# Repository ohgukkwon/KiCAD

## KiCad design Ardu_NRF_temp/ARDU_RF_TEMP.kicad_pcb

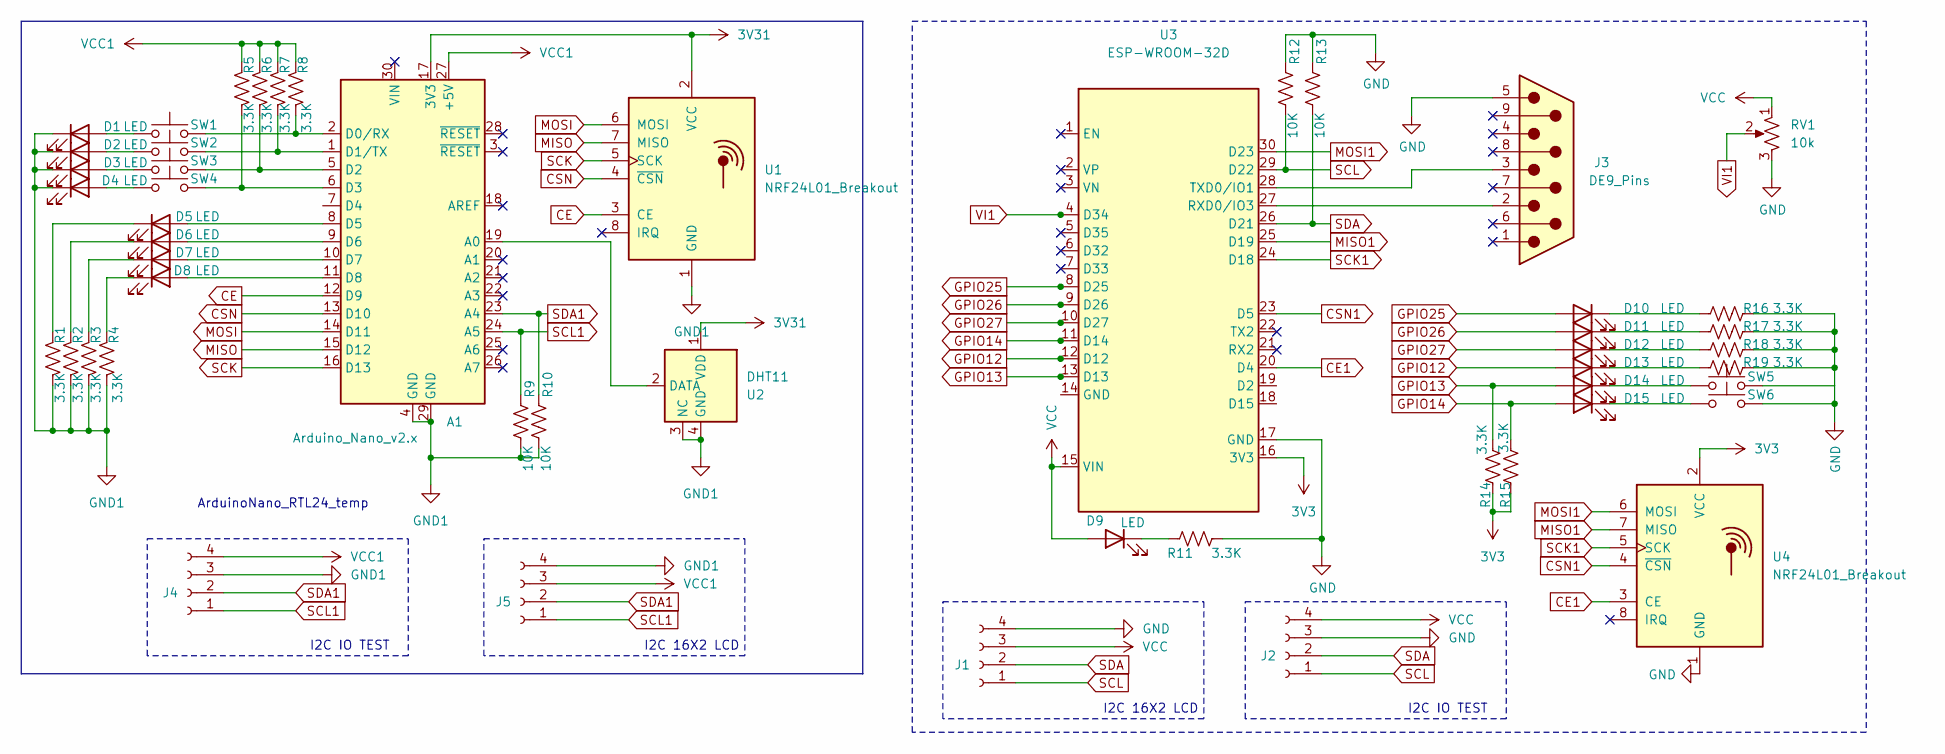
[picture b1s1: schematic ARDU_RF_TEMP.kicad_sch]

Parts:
A1: Arduino_Nano_v2.x; Arduino_Nano
D1, D2, D3, D4, D5, D6, D7, D8, D9, D10, D11, D12, D13, D14, D15: LED; LED_D3.0mm_Horizontal_O1.27mm_Z2.0mm
J1, J5: Conn_01x04_Socket; CONN_PPPC041LGBN-RC_SUL
J2, J4: Conn_01x04_Socket; CONN_PPTC041LFBN-RC_SUL
J3: DE9_Pins; DSUB-9_Pins_Vertical_P2.77x2.84mm_MountingHoles
R1, R2, R3, R4, R5, R6, R7, R8, R11, R14, R15, R16, R17, R18, R19: 3.3K; R_Axial_DIN0207_L6.3mm_D2.5mm_P10.16mm_Horizontal
R9, R10, R12, R13: 10K; R_Axial_DIN0207_L6.3mm_D2.5mm_P10.16mm_Horizontal
RV1: 10k; Potentiometer_Alps_RK163_Single_Horizontal
SW1, SW2, SW3, SW4, SW5, SW6: SW_Push; SW_Tactile_SPST_NO_Straight_CK_PTS636Sx25SMTRLFS
U1, U4: NRF24L01_Breakout; nRF24L01_Breakout
U2: DHT11; Aosong_DHT11_5.5x12.0_P2.54mm
U3: ESP-WROOM-32D

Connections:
3V3: R14.1, R15.1, U4.2 (VCC)
3V31: A1.17 (3V3), U1.2 (VCC), U2.1 (VDD)
CE: A1.12 (D9), U1.3 (CE)
CE1: U3.20 (D4), U4.3 (CE)
CSN: A1.13 (D10), U1.4 (~CSN)
CSN1: U3.23 (D5), U4.4 (~CSN)
GND: J1.4, J2.3, J3.5, R11.2, R12.1, R13.1, R16.2, R17.2, R18.2, R19.2, RV1.3, SW6.2, U3.17 (GND), U4.1 (GND)
GND1: A1.4 (GND), A1.29 (GND), D1.1 (K), D2.1 (K), D3.1 (K), D4.1 (K), J4.3, J5.4, R1.2, R2.2, R3.2, R4.2, R9.2, R10.2, U1.1 (GND), U2.3 (NC), U2.4 (GND)
GPIO12: D13.2 (A), U3.12 (D12)
GPIO13: D14.2 (A), R14.2, U3.13 (D13)
GPIO14: D15.2 (A), R15.2, U3.11 (D14)
GPIO25: D10.2 (A), U3.8 (D25)
GPIO26: D11.2 (A), U3.9 (D26)
GPIO27: D12.2 (A), U3.10 (D27)
MISO: A1.15 (D12), U1.7 (MISO)
MISO1: U3.25 (D19), U4.7 (MISO)
MOSI: A1.14 (D11), U1.6 (MOSI)
MOSI1: U3.30 (D23), U4.6 (MOSI)
unnamed: A1.19 (A0), U2.2 (DATA)
unnamed: A1.2 (D0/RX), R8.2, SW1.2
unnamed: A1.1 (D1/TX), R7.2, SW2.2
unnamed: A1.5 (D2), R6.2, SW3.2
unnamed: A1.6 (D3), R5.2, SW4.2
unnamed: A1.8 (D5), D5.2 (A)
unnamed: A1.9 (D6), D6.2 (A)
unnamed: A1.10 (D7), D7.2 (A)
unnamed: A1.11 (D8), D8.2 (A)
unnamed: D1.2 (A), SW1.1
unnamed: D2.2 (A), SW2.1
unnamed: D3.2 (A), SW3.1
unnamed: D4.2 (A), SW4.1
unnamed: D5.1 (K), R1.1
unnamed: D6.1 (K), R2.1
unnamed: D7.1 (K), R3.1
unnamed: D8.1 (K), R4.1
unnamed: D9.1 (K), R11.1
unnamed: D10.1 (K), R16.1
unnamed: D11.1 (K), R17.1
unnamed: D12.1 (K), R18.1
unnamed: D13.1 (K), R19.1
unnamed: D14.1 (K), SW5.1
unnamed: D15.1 (K), SW6.1
unnamed: J3.2, U3.27 (RXD0/IO3)
unnamed: J3.3, U3.28 (TXD0/IO1)
SCK: A1.16 (D13), U1.5 (SCK)
SCK1: U3.24 (D18), U4.5 (SCK)
SCL: J1.1, J2.1, R12.2, U3.29 (D22)
SCL1: A1.24 (A5), J4.1, J5.1, R9.1
SDA: J1.2, J2.2, R13.2, U3.26 (D21)
SDA1: A1.23 (A4), J4.2, J5.2, R10.1
VCC: D9.2 (A), J1.3, J2.4, RV1.1, U3.15 (VIN)
VCC1: A1.27 (+5V), J4.4, J5.3, R5.1, R6.1, R7.1, R8.1
VI1: RV1.2, U3.4 (D34)

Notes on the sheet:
I2C 16X2 LCD
I2C IO TEST
ArduinoNano_RTL24_temp

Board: 2 copper layers, 51 parts (0 on the bottom side), 53 nets, no tracks yet.

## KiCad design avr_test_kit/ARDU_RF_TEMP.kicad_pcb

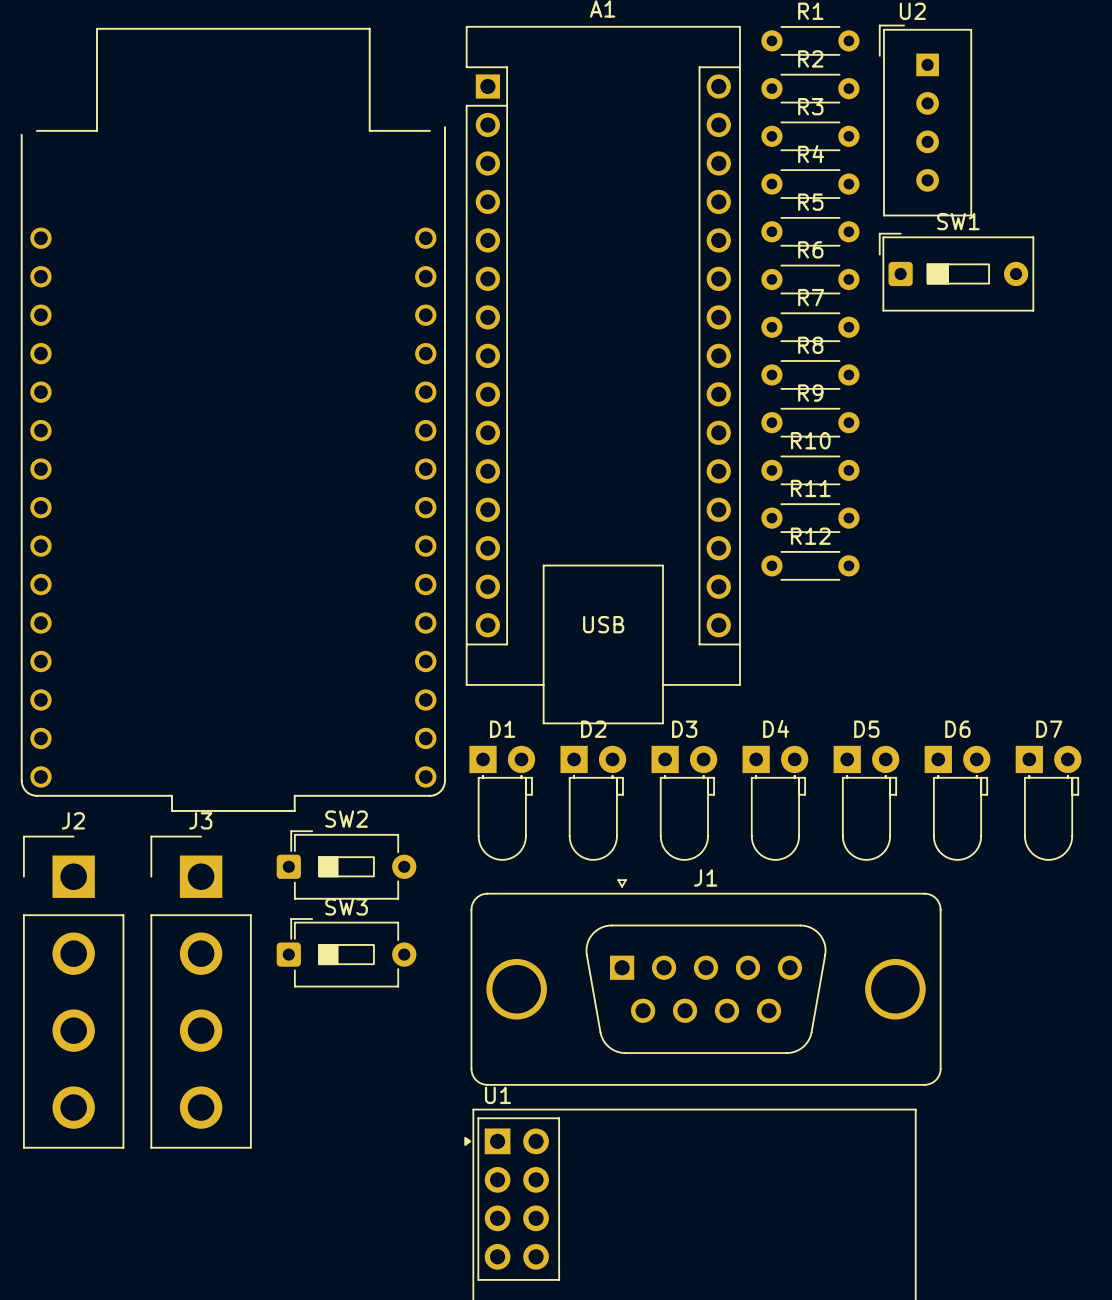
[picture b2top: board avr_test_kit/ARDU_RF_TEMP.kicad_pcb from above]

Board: 2 copper layers, 29 parts (0 on the bottom side), 28 nets, no tracks yet.

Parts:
A1: Arduino_Nano_v2.x; Arduino_Nano
D1, D2, D3, D4, D5, D6, D7: LED; LED_D3.0mm_Horizontal_O1.27mm_Z2.0mm
J1: DE9_Pins; DSUB-9_Pins_Vertical_P2.77x2.84mm_MountingHoles
J2, J3: Conn_01x04_Socket; Samtec_HPM-04-01-x-S_Straight_1x04_Pitch5.08mm
R1, R9, R10, R11, R12: 10K; R_Axial_DIN0204_L3.6mm_D1.6mm_P5.08mm_Horizontal
R2, R3, R4, R5, R6, R7, R8: 3.3K; R_Axial_DIN0204_L3.6mm_D1.6mm_P5.08mm_Horizontal
SW1: SW_DIP_x01; SW_DIP_SPSTx01_Slide_9.78x4.72mm_W7.62mm_P2.54mm
SW2, SW3: SW_Push; SW_DIP_SPSTx01_Slide_6.7x4.1mm_W7.62mm_P2.54mm_LowProfile
U1: NRF24L01_Breakout; nRF24L01_Breakout
U2: DHT11; Aosong_DHT11_5.5x12.0_P2.54mm
U3: ESP-WROOM-32D

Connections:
3V3: A1.17 (3V3), U1.2 (VCC), U2.1 (VDD)
CE: A1.12 (D9), U1.3 (CE)
CSN: A1.13 (D10), U1.4 (~CSN)
GND: A1.4 (GND), A1.27 (+5V), A1.29 (GND), J1.5, J2.3, J2.4, J3.3, J3.4, R1.1, R2.2, R3.2, R4.2, R5.2, R6.2, R7.2, R8.2, R9.2, R10.2, R11.2, R12.2, SW1.1, U1.1 (GND), U2.4 (GND), U3.GND
GPIO12: D5.2 (A), U3.14 (IO12)
GPIO13: SW2.1, U3.16 (IO13)
GPIO14: SW3.1, U3.13 (IO14)
GPIO25: D2.2 (A), U3.10 (IO25)
GPIO26: D3.2 (A), U3.11 (IO26)
GPIO27: D4.2 (A), U3.12 (IO27)
MISO: A1.15 (D12), U1.7 (MISO)
MOSI: A1.14 (D11), U1.6 (MOSI)
unnamed: A1.19 (A0), U2.2 (DATA)
unnamed: D1.2 (A), R1.2, SW1.2, U3.3 (EN), U3.VIN (VIN_5V)
unnamed: D1.1 (K), R2.1
unnamed: D2.1 (K), R3.1
unnamed: D3.1 (K), R4.1
unnamed: D4.1 (K), R5.1
unnamed: D5.1 (K), R6.1
unnamed: D6.2 (A), SW2.2
unnamed: D6.1 (K), R7.1
unnamed: D7.2 (A), SW3.2
unnamed: D7.1 (K), R8.1
unnamed: J1.2, U3.34 (RXD0/IO3)
unnamed: J1.3, U3.35 (TXD0/IO1)
SCK: A1.16 (D13), U1.5 (SCK)
SCL: J2.1, J3.1, R10.1, R12.1, U3.36 (SCL/IO22)
SDA: J2.2, J3.2, R9.1, R11.1, U3.33 (SDA/IO21)

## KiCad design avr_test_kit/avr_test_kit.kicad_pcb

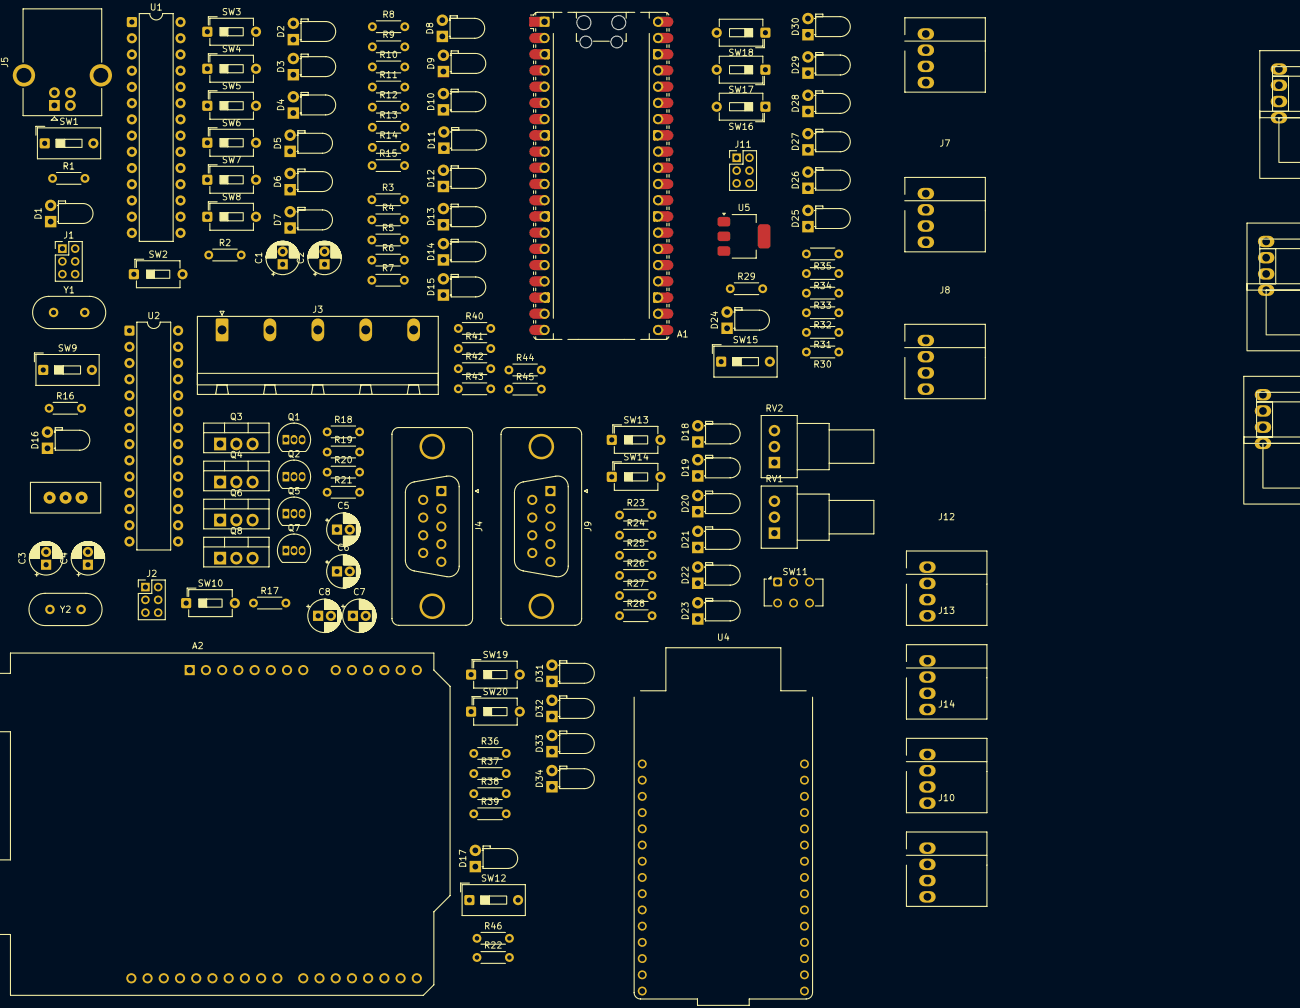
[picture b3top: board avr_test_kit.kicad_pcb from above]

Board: 2 copper layers, 144 parts (0 on the bottom side), 116 nets, no tracks yet.

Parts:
A1: RaspberryPi_Pico; RaspberryPi_Pico_Common_Unspecified
A2: Arduino_UNO_R3
C1, C2, C3, C4: 22pF; CP_Radial_D5.0mm_P2.00mm
C5, C6, C7, C8: 1UF; CP_Radial_D5.0mm_P2.00mm
D1, D2, D3, D4, D5, D6, D7, D8, D9, D10, D11, D12, D13, D14, D15, D16, D17, D18, D19, D20, D21, D22, D23, D24, D25, D26, D27, D28, D29, D30, D31, D32, D33, D34: LED; LED_D3.0mm_Horizontal_O1.27mm_Z2.0mm
DS1, DS2, DS3: LCD_16X2_I2C VERTICAL; LCD 16X2 I2C
J1, J2, J11: ICSP_ISP6; PinHeader_2x03_P2.00mm_Vertical
J3: Conn_01x05; PhoenixContact_GMSTBA_2,5_5-G_1x05_P7.50mm_Horizontal
J4, J9: DE9_Pins; DSUB-9_Pins_Vertical_P2.77x2.84mm_MountingHoles
J5: USB_B; USB_B_OST_USB-B1HSxx_Horizontal
J6, J7, J8, J10, J12, J13, J14: Conn_01x04_Socket; Conn_4x1_90deg_angle
Q1, Q2, Q5, Q7: PN2222A; TO-92_Inline
Q3, Q4, Q6, Q8: IRF4905; TO-220-3_Vertical
R1, R3, R4, R5, R6, R7, R8, R9, R10, R11, R12, R13, R14, R15, R16, R22, R23, R24, R25, R26, R27, R28, R29, R30, R31, R32, R33, R34, R35, R36, R37, R38, R39: 3.3K; R_Axial_DIN0204_L3.6mm_D1.6mm_P5.08mm_Horizontal
R2, R17, R40, R41, R42, R43, R44, R45, R46: 10K; R_Axial_DIN0204_L3.6mm_D1.6mm_P5.08mm_Horizontal
R18, R19, R20, R21: 100; R_Axial_DIN0204_L3.6mm_D1.6mm_P5.08mm_Horizontal
RV1, RV2: 10k; Potentiometer_Alps_RK09Y11_Single_Horizontal
SW1, SW9, SW12, SW15: SW_DIP_x01; SW_DIP_SPSTx01_Slide_9.78x4.72mm_W7.62mm_P2.54mm
SW2, SW3, SW4, SW5, SW6, SW7, SW8, SW10, SW13, SW14, SW16, SW17, SW18, SW19, SW20: SW_Push; SW_DIP_SPSTx01_Slide_6.7x4.1mm_W7.62mm_P2.54mm_LowProfile
SW11: SW_Slide_DPDT; SW_CK_JS202011CQN_DPDT_Straight
U1, U2: ATmega328-P; DIP-28_W7.62mm
U3: L7805; LM7805
U4: ESP-WROOM-32D
U5: AMS1117-3.3; SOT-223-3_TabPin2
Y1, Y2: 16MHz; Crystal_HC49-4H_Vertical

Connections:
5V: R18.1, R19.1, R20.1, R21.1, U3.3 (OUT)
A0: A2.9 (A0), J10.2, RV1.2, U4.7 (IO35)
A1: A2.10 (A1), J10.1, RV2.2, U4.6 (IO34)
GND: A1.3 (GND), A1.8 (GND), A1.13 (GND), A1.18 (GND), A1.23 (GND), A1.28 (GND), A1.38 (GND), A2.7 (GND), C1.2, C2.2, C3.2, C4.2, C5.2, C6.2, C7.2, C8.2, D5.1 (K), J1.6, J2.6, J4.5, J5.4 (GND), J6.1, J7.1, J8.1, J9.5, J12.4, J13.4, J14.4, Q1.1 (E), Q2.1 (E), Q3.2 (D), Q4.2 (D), Q5.1 (E), Q6.2 (D), Q7.1 (E), Q8.2 (D), R1.2, R3.2, R4.2, R5.2, R6.2, R7.2, R8.2, R9.2, R10.2, R11.2, R12.2, R13.2, R14.2, R15.2, R16.2, R22.2, R23.2, R24.2, R25.2, R26.2, R27.2, R28.2, R29.2, R30.2, R31.2, R32.2, R33.2, R34.2, R35.2, R36.1, R37.1, R38.1, R39.1, R46.1, RV1.3, RV2.3, SW2.2, SW10.2, U1.8 (GND), U1.22 (GND), U2.8 (GND), U2.22 (GND), U3.2 (GND), U4.GND, U5.1 (GND)
GPIO12: D21.2 (A), U4.14 (IO12)
GPIO13: SW13.1, U4.16 (IO13)
GPIO14: SW14.1, U4.13 (IO14)
GPIO25: D18.2 (A), U4.10 (IO25)
GPIO26: D19.2 (A), U4.11 (IO26)
GPIO27: D20.2 (A), U4.12 (IO27)
MISO: J1.1, U1.18 (PB4)
MOSI: J1.4, U1.17 (PB3)
MOSI_PI: A1.25 (GPIO19), J11.3
unnamed: A1.1 (GPIO0), SW18.1
unnamed: A1.2 (GPIO1), SW17.1
unnamed: A1.4 (GPIO2), SW16.1
unnamed: A1.5 (GPIO3), D27.2 (A)
unnamed: A1.6 (GPIO4), D26.2 (A)
unnamed: A1.7 (GPIO5), D25.2 (A)
unnamed: A1.39 (VSYS), U5.2 (VO)
unnamed: D1.2 (A), SW1.2, U1.7 (VCC)
unnamed: D1.1 (K), R1.1
unnamed: D2.2 (A), SW3.2
unnamed: D2.1 (K), R3.1
unnamed: D3.2 (A), SW4.2
unnamed: D3.1 (K), R4.1
unnamed: D4.2 (A), SW5.2
unnamed: D4.1 (K), R5.1
unnamed: D5.2 (A), SW6.2
unnamed: D6.2 (A), SW7.2
unnamed: D6.1 (K), R6.1
unnamed: D7.2 (A), SW8.2
unnamed: D7.1 (K), R7.1
unnamed: D8.2 (A), U1.2 (PD0)
unnamed: D8.1 (K), R8.1
unnamed: D9.2 (A), U1.3 (PD1)
unnamed: D9.1 (K), R9.1
unnamed: D10.2 (A), U1.4 (PD2)
unnamed: D10.1 (K), R10.1
unnamed: D11.2 (A), U1.5 (PD3)
unnamed: D11.1 (K), R11.1
unnamed: D12.2 (A), U1.6 (PD4)
unnamed: D12.1 (K), R12.1
unnamed: D13.2 (A), U1.11 (PD5)
unnamed: D13.1 (K), R13.1
unnamed: D14.2 (A), U1.12 (PD6)
unnamed: D14.1 (K), R14.1
unnamed: D15.2 (A), U1.13 (PD7)
unnamed: D15.1 (K), R15.1
unnamed: D16.2 (A), SW9.2, U2.7 (VCC)
unnamed: D16.1 (K), R16.1
unnamed: D17.2 (A), SW12.2, U4.VIN (VIN_5V)
unnamed: D17.1 (K), R22.1
unnamed: D18.1 (K), R23.1
unnamed: D19.1 (K), R24.1
unnamed: D20.1 (K), R25.1
unnamed: D21.1 (K), R26.1
unnamed: D22.2 (A), SW13.2
unnamed: D22.1 (K), R27.1
unnamed: D23.2 (A), SW14.2
unnamed: D23.1 (K), R28.1
unnamed: D24.2 (A), SW15.2, U5.3 (VI)
unnamed: D24.1 (K), R29.1
unnamed: D25.1 (K), R30.1
unnamed: D26.1 (K), R31.1
unnamed: D27.1 (K), R32.1
unnamed: D28.2 (A), SW16.2
unnamed: D28.1 (K), R33.1
unnamed: D29.2 (A), SW17.2
unnamed: D29.1 (K), R34.1
unnamed: D30.2 (A), SW18.2
unnamed: D30.1 (K), R35.1
unnamed: D31.2 (A), SW19.2
unnamed: D31.1 (K), R36.2
unnamed: D32.2 (A), SW20.2
unnamed: D32.1 (K), R37.2
unnamed: D33.1 (K), R38.2
unnamed: D34.1 (K), R39.2
unnamed: J2.1, U2.18 (PB4)
unnamed: J2.3, U2.19 (PB5)
unnamed: J2.4, U2.17 (PB3)
unnamed: J2.5, R17.2, SW10.1, U2.1 (~RESET/PC6)
unnamed: J3.2, Q3.3 (S)
unnamed: J3.3, Q4.3 (S)
unnamed: J3.4, Q6.3 (S)
unnamed: J3.5, Q8.3 (S)
unnamed: J5.1 (VBUS), SW11.1 (A)
unnamed: Q1.3 (C), Q3.1 (G), R18.2
unnamed: Q2.3 (C), Q4.1 (G), R19.2
unnamed: Q5.3 (C), Q6.1 (G), R20.2
unnamed: Q7.3 (C), Q8.1 (G), R21.2
unnamed: SW6.1, U1.14 (PB0)
unnamed: SW7.1, U1.15 (PB1)
unnamed: SW8.1, U1.16 (PB2)
unnamed: SW3.1, U1.23 (PC0)
unnamed: SW4.1, U1.24 (PC1)
unnamed: SW5.1, U1.25 (PC2)
unnamed: C2.1, U1.9 (XTAL1/PB6), Y1.2
unnamed: C1.1, U1.10 (XTAL2/PB7), Y1.1
unnamed: C4.1, U2.9 (XTAL1/PB6), Y2.2
unnamed: C3.1, U2.10 (XTAL2/PB7), Y2.1
unnamed: J9.2, U4.34 (RXD0/IO3)
unnamed: J9.3, U4.35 (TXD0/IO1)
PWM1: C5.1, Q1.2 (B), U2.11 (PD5)
PWM2: C6.1, Q2.2 (B), U2.12 (PD6)
PWM3: C7.1, Q5.2 (B), U2.15 (PB1)
PWM4: C8.1, Q7.2 (B), U2.16 (PB2)
RESET: J1.5, R2.2, SW2.1, U1.1 (~RESET/PC6)
RXD: J4.2, U2.2 (PD0)
SCK: J1.3, U1.19 (PB5)
SCL: A1.17 (GPIO13), A2.14 (SCL/A5), J6.4, J7.4, J8.4, J12.1, J13.1, J14.1, R41.1, R43.1, R45.1, U1.28 (PC5), U2.28 (PC5), U4.36 (SCL/IO22)
SDA: A1.16 (GPIO12), A2.13 (SDA/A4), J6.3, J7.3, J8.3, J12.2, J13.2, J14.2, R40.1, R42.1, R44.1, U1.27 (PC4), U2.27 (PC4), U4.33 (SDA/IO21)
TXD: J4.3, U2.3 (PD1)
VO11: J10.4, U4.9 (IO33)
VO12: J10.3, U4.8 (IO32)
VTG: J1.2, J2.2, J6.2, J7.2, J8.2, J11.5, J12.3, J13.3, J14.3, R2.1, R17.1, R40.2, R41.2, R42.2, R43.2, R44.2, R45.2, R46.2, RV1.1, RV2.1, SW1.1, SW9.1, SW11.2 (B), SW12.1, SW15.1, U1.20 (AVCC), U2.20 (AVCC), U3.1 (IN), U4.3 (EN)

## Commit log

2025-05-10 5/10/25
2025-05-11 5/10/25-2
2025-05-22 5/21/25-1
